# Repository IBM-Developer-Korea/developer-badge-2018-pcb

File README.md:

# Badge PCB

This repository contains schematic, PCB and BoM for Developer Day 2018 Badge

[KiCAD 5](http://kicad-pcb.org/download/) is used to design.

## 3D modeling

## Errata

* v1.0: in J9(HSPI), silk for +/- should be swapped. Correct pin is +(VCC), -(GND), GPIO14, GPIO12, GPIO13, GPIO15.

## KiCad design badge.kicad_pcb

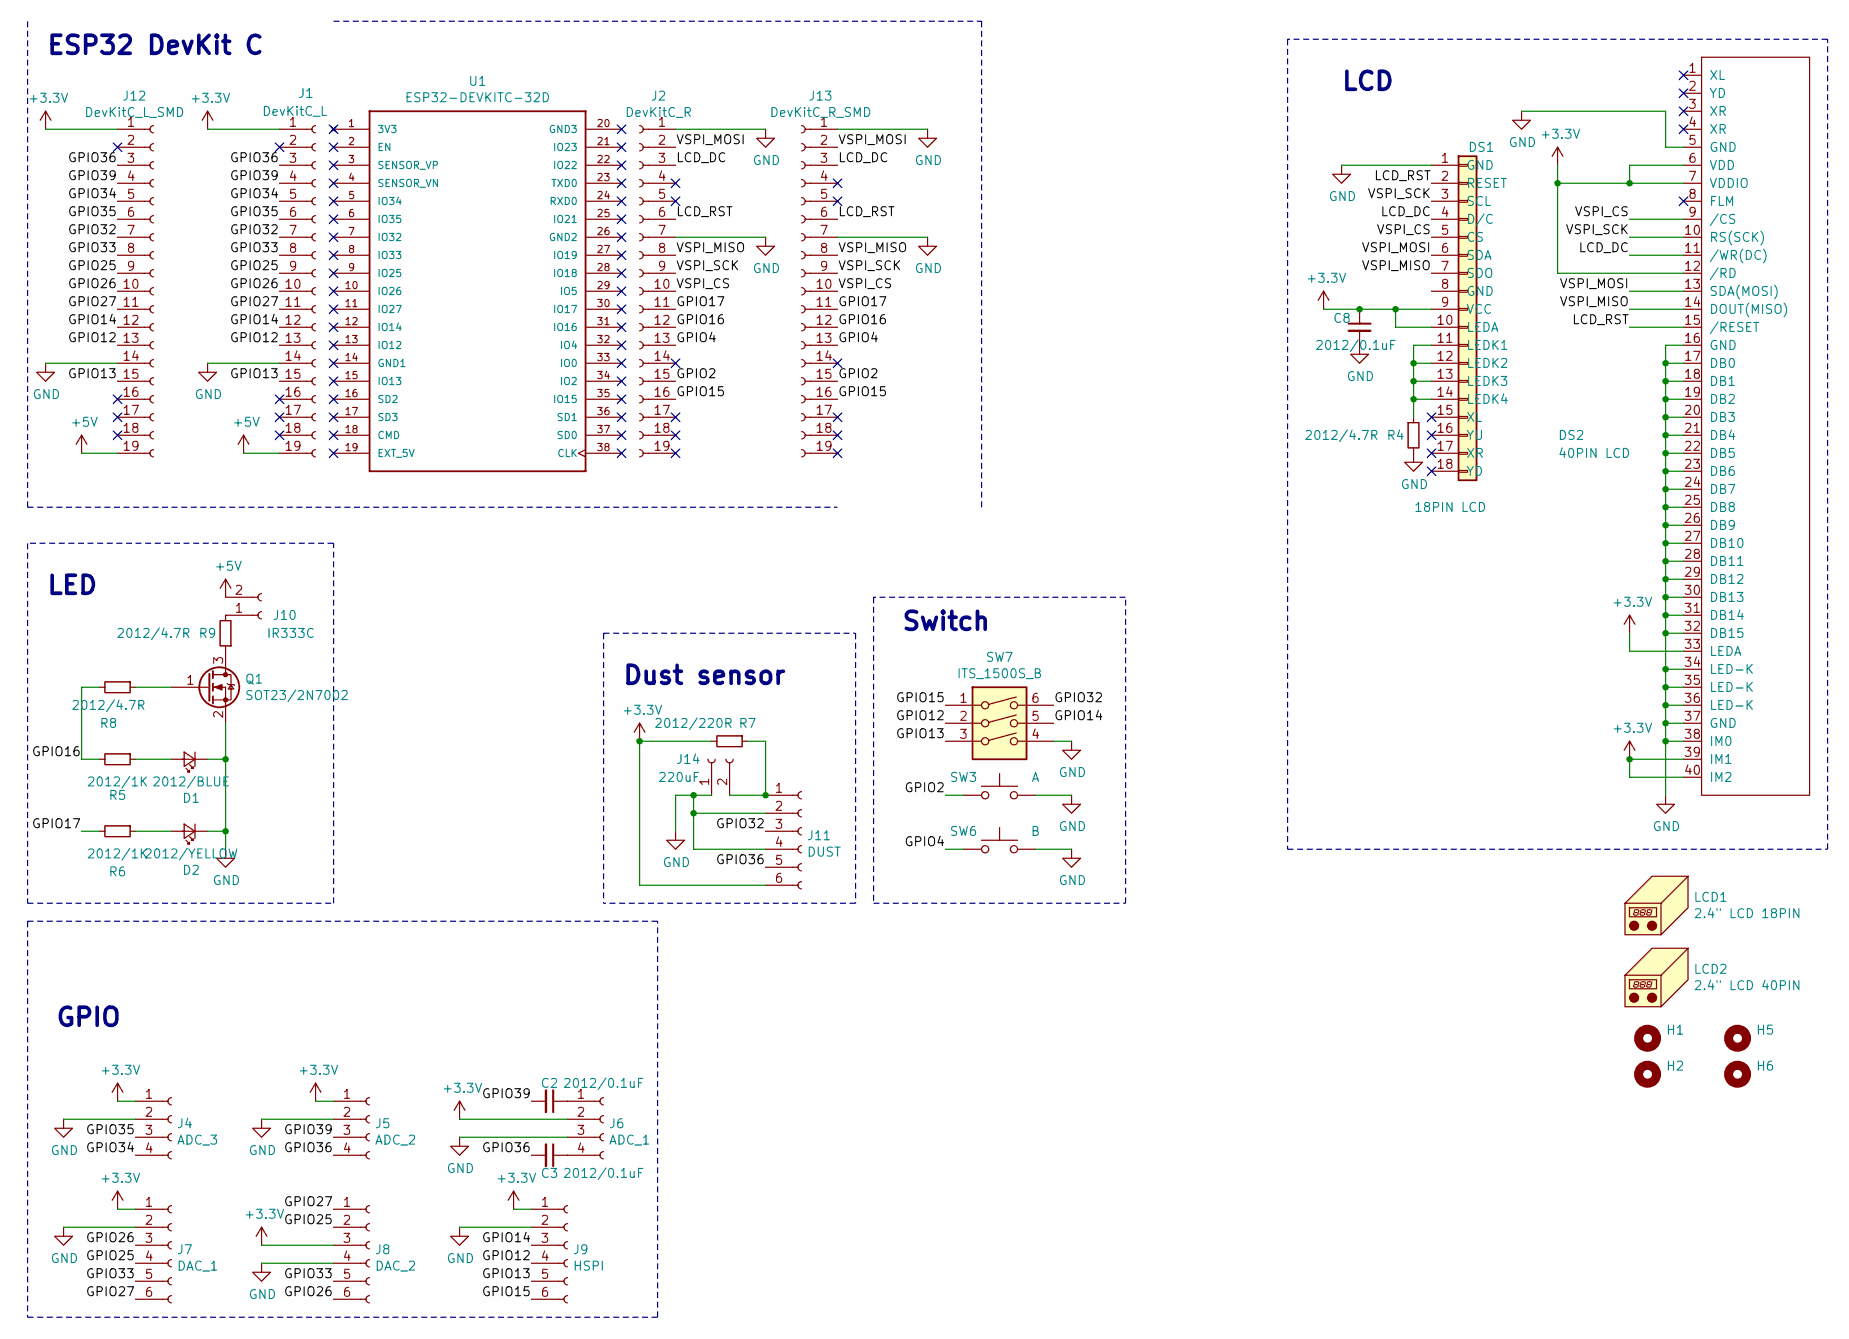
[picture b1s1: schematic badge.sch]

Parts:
C2, C3, C8: 2012/0.1uF; C_0805_2012Metric
D1: 2012/BLUE; LED_0805_2012Metric
D2: 2012/YELLOW; LED_0805_2012Metric
DS1: 18PIN LCD; COMMON_MOUNT_FFC-1x18-1MP_P0.80mm
DS2: 40PIN LCD; Yeonho_05002HR-40C_1x40-1MP_P0.50mm_Horizontal
H1, H2, H5, H6: MountingHole; LanyardHole_6mm
J1: DevKitC_L; PinSocket_1x19_P2.54mm_Vertical_Universal_Pin1Right
J2: DevKitC_R; PinSocket_1x19_P2.54mm_Vertical_BackOnly_NO3D
J4: ADC_3; PinSocket_1x04_P2.54mm_Vertical_NO3D_1S
J5: ADC_2; PinSocket_1x04_P2.54mm_Vertical_NO3D_1S
J6: ADC_1; PinSocket_1x04_P2.54mm_Vertical_NO3D_2S
J7: DAC_1; PinSocket_1x06_P2.54mm_Vertical_NO3D_1S
J8: DAC_2; PinSocket_1x06_P2.54mm_Vertical_NO3D_3S
J9: HSPI; PinSocket_1x06_P2.54mm_Vertical_NO3D_5S
J10: IR333C; PinSocket_1x02_P2.54mm_Vertical_NO3D
J11: DUST; PinSocket_1x06_P2.54mm_Vertical_NO3D
J12: DevKitC_L_SMD; PinSocket_1x19_P2.54mm_Vertical_SMD_Pin1Right
J13: DevKitC_R_SMD; PinSocket_1x19_P2.54mm_Vertical_SMD_Pin1Left
J14: 220uF; PinSocket_1x02_P2.54mm_Vertical_NO3D
LCD1: 2.4\" LCD 18PIN; 2.4INCH_TFT_LCD_18P_0.80mm_FOLD_JGKONG
LCD2: 2.4\" LCD 40PIN; 2.4INCH_TFT_LCD_40P_0.50mm_FOLD
Q1: SOT23/2N7002; SOT-23
R4, R8, R9: 2012/4.7R; R_0805_2012Metric
R5, R6: 2012/1K; R_0805_2012Metric
R7: 2012/220R; R_0805_2012Metric
SW3: A; ITS-1103S
SW6: B; ITS-1103S
SW7: ITS_1500S_B; ITS-1500S-B-SILKDIR
U1: ESP32-DEVKITC-32D; MODULE_ESP32-DEVKITC-32D-SILKONLY-SIMPLE

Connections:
+3V3: C8.1, DS1.9 (VCC), DS1.10 (LEDA), DS2.6 (VDD), DS2.7 (VDDIO), DS2.12 (/RD), DS2.33 (LEDA), DS2.39 (IM1), DS2.40 (IM2), J1.1, J4.1, J5.1, J6.2, J7.1, J8.3, J9.1, J11.6, J12.1, R7.2
+5V: J1.19, J10.2, J12.19
/GPIO2: J2.15, J13.15, SW3.1
/GPIO4: J2.13, J13.13, SW6.1
/GPIO12: J1.13, J9.4, J12.13, SW7.2
/GPIO13: J1.15, J9.5, J12.15, SW7.3
/GPIO14: J1.12, J9.3, J12.12, SW7.5
/GPIO15: J2.16, J9.6, J13.16, SW7.1
/GPIO16: J2.12, J13.12, R5.2, R8.2
/GPIO17: J2.11, J13.11, R6.2
/GPIO25: J1.9, J7.4, J8.2, J12.9
/GPIO26: J1.10, J7.3, J8.6, J12.10
/GPIO27: J1.11, J7.6, J8.1, J12.11
/GPIO32: J1.7, J11.3, J12.7, SW7.6
/GPIO33: J1.8, J7.5, J8.5, J12.8
/GPIO34: J1.5, J4.4, J12.5
/GPIO35: J1.6, J4.3, J12.6
/GPIO36: C3.2, J1.3, J5.4, J11.5, J12.3
/GPIO39: C2.2, J1.4, J5.3, J12.4
/LCD_DC: DS1.4 (D/C), DS2.11 (/WR(DC)), J2.3, J13.3
/LCD_RST: DS1.2 (RESET), DS2.15 (/RESET), J2.6, J13.6
/VSPI_CS: DS1.5 (CS), DS2.9 (/CS), J2.10, J13.10
/VSPI_MISO: DS1.7 (SDO), DS2.14 (DOUT(MISO)), J2.8, J13.8
/VSPI_MOSI: DS1.6 (SDA), DS2.13 (SDA(MOSI)), J2.2, J13.2
/VSPI_SCK: DS1.3 (SCL), DS2.10 (RS(SCK)), J2.9, J13.9
GND: C8.2, D1.1 (K), D2.1 (K), DS1.1 (GND), DS2.5 (GND), DS2.16 (GND), DS2.17 (DB0), DS2.18 (DB1), DS2.19 (DB2), DS2.20 (DB3), DS2.21 (DB4), DS2.22 (DB5), DS2.23 (DB6), DS2.24 (DB7), DS2.25 (DB8), DS2.26 (DB9), DS2.27 (DB10), DS2.28 (DB11), DS2.29 (DB12), DS2.30 (DB13), DS2.31 (DB14), DS2.32 (DB15), DS2.34 (LED-K), DS2.35 (LED-K), DS2.36 (LED-K), DS2.37 (GND), DS2.38 (IM0), J1.14, J2.1, J2.7, J4.2, J5.2, J6.3, J7.2, J8.4, J9.2, J11.2, J11.4, J12.14, J13.1, J13.7, J14.1, Q1.2 (S), R4.2, SW3.2, SW6.2, SW7.4
unnamed: C2.1, J6.1
unnamed: C3.1, J6.4
unnamed: D1.2 (A), R5.1
unnamed: D2.2 (A), R6.1
unnamed: DS1.11 (LEDK1), DS1.12 (LEDK2), DS1.13 (LEDK3), DS1.14 (LEDK4), R4.1
unnamed: J10.1, R9.2
unnamed: J11.1, J14.2, R7.1
unnamed: Q1.1 (G), R8.1
unnamed: Q1.3 (D), R9.1

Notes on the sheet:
LCD
ESP32 DevKit C
GPIO
Switch
LED
Dust sensor

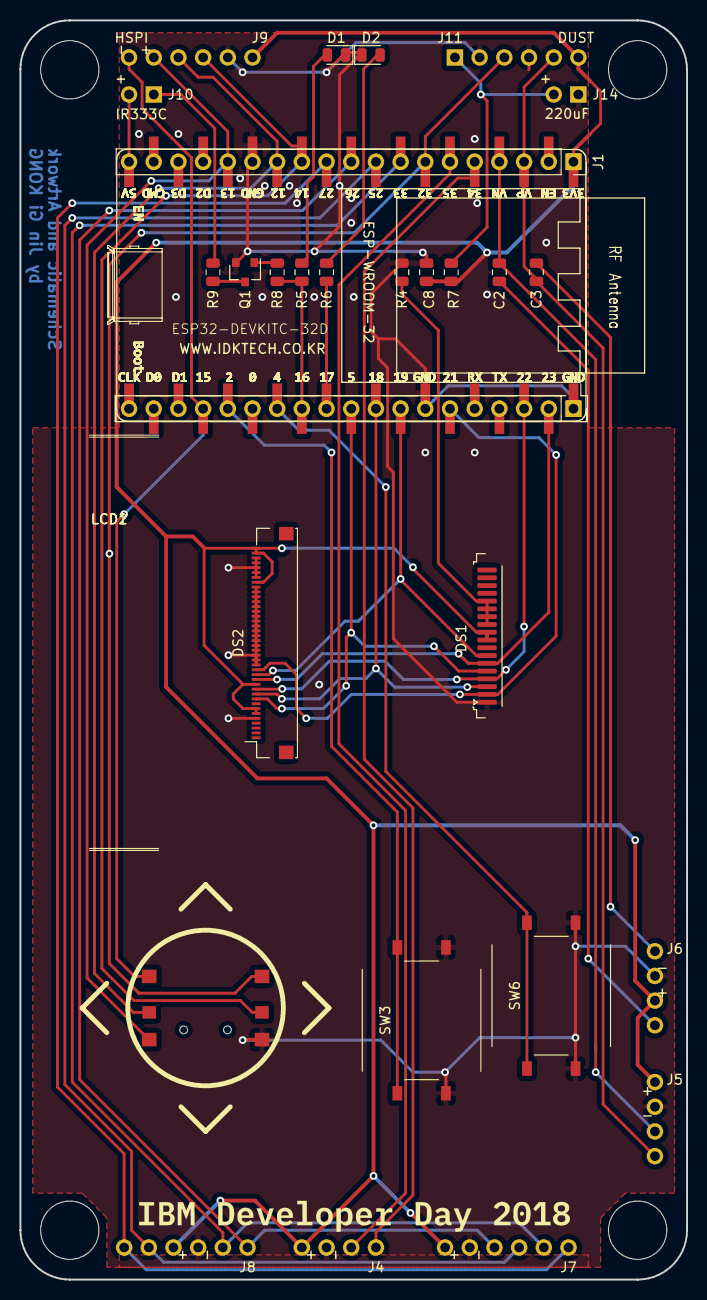
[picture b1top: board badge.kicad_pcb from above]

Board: 2 copper layers, 68.6 x 129.5 mm, 36 parts (0 on the bottom side), 35 nets.

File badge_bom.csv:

Item,Qty,Reference(s),Value,LibPart,Footprint,Datasheet,Field4,Field5,Field6,Field7,Field8
1,2,"C2, C8",2012/0.1uF,C_Small,C_0805,,,,,,
2,1,C3,2012/100nF,C_Small,C_0805,,,,,,
3,1,D1,2012/BLUE,LED_Small,LED_0805,,,,,,
4,1,D2,2012/YELLOW,LED_Small,LED_0805,,,,,,
5,1,DS1,18PIN LCD,LCD_SPI_18P,FFC-1x18-1MP_P0.80mm,,,,,,
6,1,DS2,40PIN LCD,HT024SQV010NH,05002HR-40C_1x40-1MP_P0.50mm_Horizontal,,,,,,
7,4,"H1, H2, H5, H6",MountingHole,MountingHole,LanyardHole_6mm,,,,,,
8,1,J1,DevKitC_L,Conn_01x19_Female,PinSocket_1x19_P2.54mm_Vertical_BackOnly,,,,,,
9,1,J2,DevKitC_R,Conn_01x19_Female,PinSocket_1x19_P2.54mm_Vertical_BackOnly,,,,,,
10,1,J4,ADC_3,Conn_01x04_Female,PinSocket_1x04_P2.54mm_Vertical,,,,,,
11,1,J5,ADC_2,Conn_01x04_Female,PinSocket_1x04_P2.54mm_Vertical,,,,,,
12,1,J6,ADC_1,Conn_01x04_Female,PinSocket_1x04_P2.54mm_Vertical,,,,,,
13,1,J7,DAC_1,Conn_01x06_Female,PinSocket_1x06_P2.54mm_Vertical,,,,,,
14,1,J8,DAC_2,Conn_01x06_Female,PinSocket_1x06_P2.54mm_Vertical,,,,,,
15,1,J9,HSPI,Conn_01x06_Female,PinSocket_1x06_P2.54mm_Vertical,,,,,,
16,1,J10,IR333C,Conn_01x02_Female,PinSocket_1x02_P2.54mm_Vertical,,,,,,
17,1,J11,DUST,Conn_01x06_Female,PinSocket_1x06_P2.54mm_Vertical,,,,,,
18,1,J12,DevKitC_L_SMD,Conn_01x19_Female,PinSocket_1x19_P2.54mm_Vertical_SMD_Pin1Right,,,,,,
19,1,J13,DevKitC_R_SMD,Conn_01x19_Female,PinSocket_1x19_P2.54mm_Vertical_SMD_Pin1Left,,,,,,
20,1,J14,220uF,Conn_01x02_Female,PinSocket_1x02_P2.54mm_Vertical,,,,,,
21,1,LCD1,"2.4"" LCD 18PIN",Housing,2.4INCH_TFT_LCD_18P_0.80mm_FOLD,,,,,,
22,1,LCD2,"2.4"" LCD 40PIN",Housing,2.4INCH_TFT_LCD_40P_0.50mm_FOLD,,,,,,
23,1,Q1,SOT23/2N7002,2N7002,SOT-23,https://www.fairchildsemi.com/datasheets/2N/2N7002.pdf,,,,,
24,3,"R4, R8, R9",2012/4.7R,R_Small,R_0805_2012Metric,,,,,,
25,2,"R5, R6",2012/1K,R_Small,R_0805_2012Metric,,,,,,
26,1,R7,2012/220R,R_Small,R_0805_2012Metric,,,,,,
27,1,SW3,ITS-1103S,SW_Push,ITS-1103S,,ILOSAM,,,,
28,1,SW6,ITS-1103S,SW_Push,ITS-1103S,,ILOSAM,,,,
29,1,SW7,ITS_1500S_B,SW_5WAY,ITS-1500S-B,,ILOSAM,,,,
30,1,U1,ESP32-DEVKITC-32D,ESP32-DEVKITC-32D,MODULE_ESP32-DEVKITC-32D-SILKONLY-SIMPLE,None,Espressif Systems,ESP32-DEVKITC-32D,None,Eval Board For Esp-Wroom-32,Unavailable

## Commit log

2018-10-28 Add btn, jumpers
2018-10-29 Change to manual PCB
2018-10-29 Square layout
2018-10-29 Arranged to v0.1
2018-10-30 v0.2 add dust sensor and 5 way tact switch
    * LED direction corrected
    * Pin adjusted
2018-10-31 v0.3 0.3mm track, SMT/THT pinsocket support
2018-10-31 Vertical badge style
    * Change C9 footprint to 2816
    * Add 3D model for 5 wat tactile switch
    * 3D models should be located in ${HOME}/kicad/template
2018-11-02 Modify footprints for Silk, add IR333C
2018-11-02 Change button
2018-11-03 Update v0.4, vertical long before tracks
    * Move footprint library to DeveloperDay2018Badge
    * Add symbol library, 3D models into project
    * Change board color
    * Increase R, C, LED size to 0805(2012)
    * Remove front solder mask for ESP32 DevKitC socket header, to make clean SMD socket pad.
    * Add silk for ESP32 DevKitC
2018-11-04 Rout'ing
    * Add dummy pad for ESP32 DevKitC footprint to avoid errors
    * Add silk guide for LCD attachment
    * Add alternative 40pin LCD connector
    * Add logo and information in silk layer
2018-11-04 v0.5 Finish tracks, final review
    * Remove paste at 18pin LCD
2018-11-05 v1.0 release
    * Update 40pin footprint
    * Update tracks
2018-11-07 Fix 3D model path into project
    * Change R values
    * Fix a few tracks
2018-11-28 Add license and other documents
2018-11-29 Remove 3D models
2018-12-13 Add badge BoM
2018-12-13 Add 3D modeling images to readme
2018-12-13 Add errata for v1.0
